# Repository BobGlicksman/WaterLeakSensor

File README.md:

# WaterLeakDetector - Version 2
The Water Leak Detector (WLD) is an IoT device that can monitor two specific locations for the presence of water. 
When water is detected, an alarm will sound and an SMS text alert will be sent to the user's mobile phone. 

A typical use case is to deploy the WLD in a laundry room where it can monitor water leaks that might occur from a washing machine, 
hot water heater, or sewer backup.

The WLD also includes a temperature and humidity sensor. These values are displayed on a dial and also in a smartphone app.  The
smartphone app (Android only at this time) is included in this project.  High and low temperature limits may be set via the smartphone
app.  When either limit is hit, an SMS text alert will be sent to the user's mobile phone.  The smartphone app allows the user to set the
high and low temperature limits.  The app displays the current temperature, relative humidity, and the status of all three alarms (low
temperature, high temperature, water leak).

This version (version 2) of the WLD eliminates Blynk and IFTTT integrations in favor or our current standard techniques for app development,
alarms and alerts, and for logging to Google cloud spreadsheets.  For details, see: 

https://github.com/TeamPracticalProjects/Connectivity_Tools_with_Particle_Devices

Begin with the file WLD Read Me First.pdf

<!---  -->

<!---  -->

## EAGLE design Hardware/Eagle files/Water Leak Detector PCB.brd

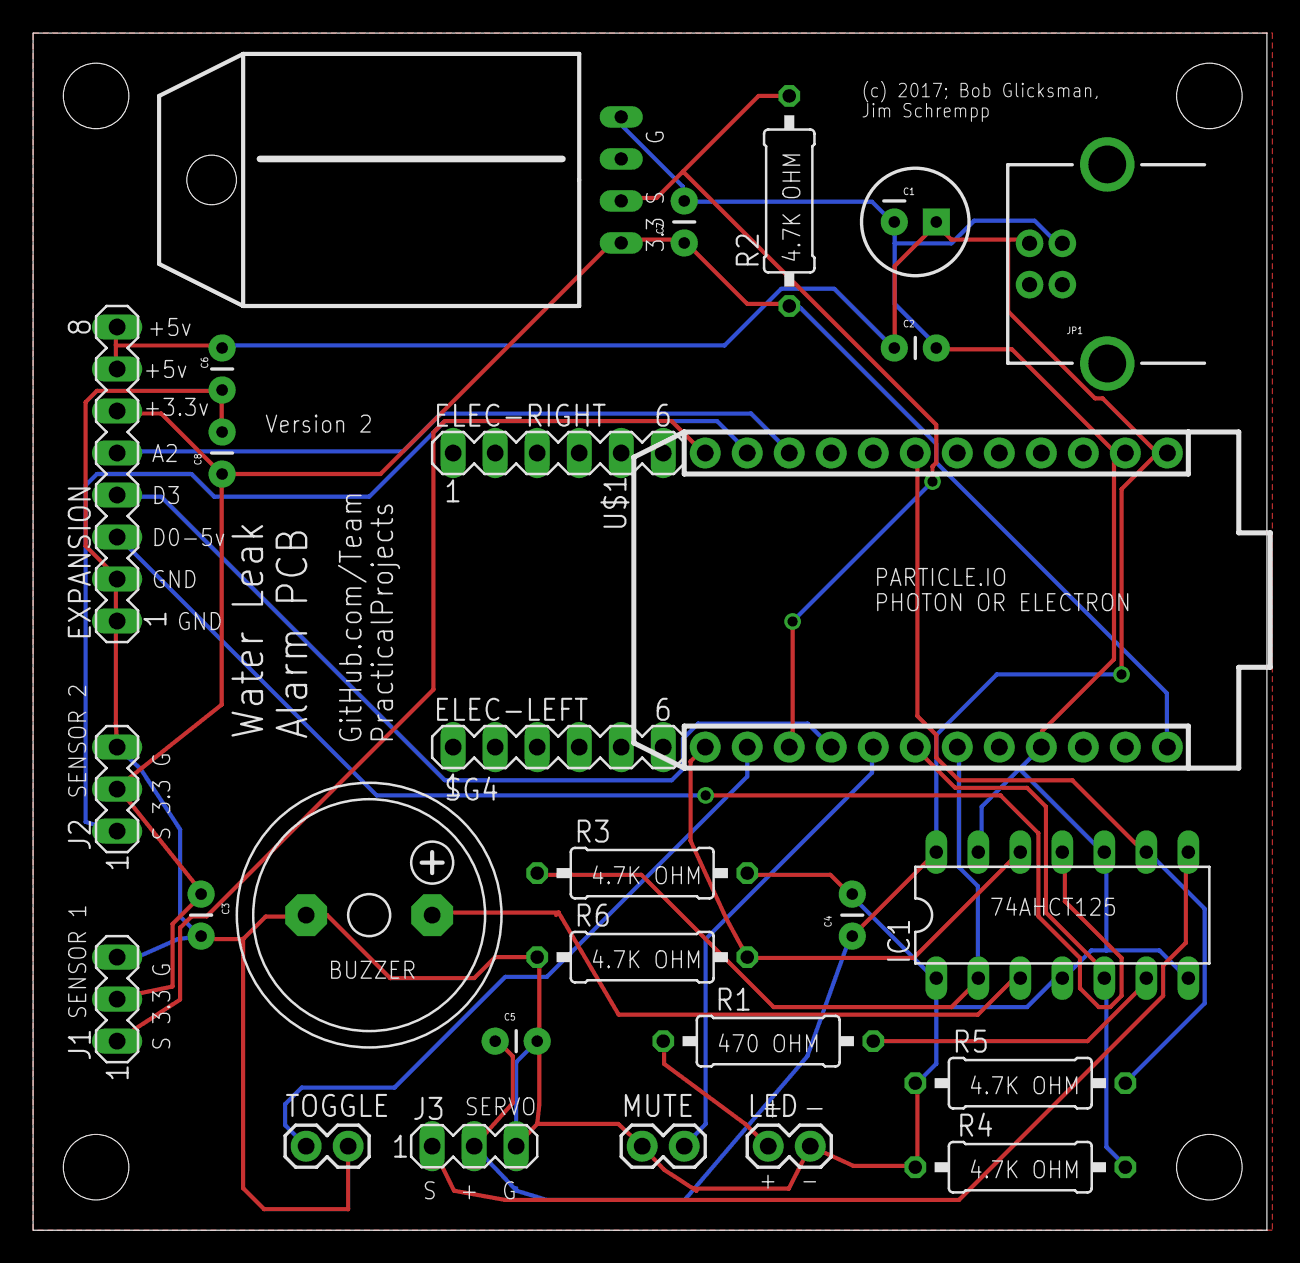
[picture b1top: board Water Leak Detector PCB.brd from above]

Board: 2 copper layers, 74.6 x 72.4 mm, 28 parts (0 on the bottom side), 19 nets.

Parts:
C1: 100uf; CPOL-RADIAL-100UF-25V
C2, C3, C4, C5, C6, C7, C8: 0.1 uF; CAP-PTH-SMALL
ELEC-LEFT: MA06-1
ELEC-RIGHT: MA06-1
EXPANSION: MA08-1
IC1: 74AHCT125; DIL14
J1: Sensor 1; MA03-1
J2: Sensor 2; MA03-1
J3: SERVO; MA03-1
JP1: USB-B; USB-B-PTH
LED: 1X02
MUTE: 1X02
R1: 470; 0309/12
R2, R3, R4, R5, R6: 4.7K; 0309/12
SG4: F/HMB
TOGGLE: 1X02
U$1: PHOTON_WITH_HEADERS; PHOTON
U$2: DHT22

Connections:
+3.3V: C3.1, C7.1, C8.1, EXPANSION.6, J1.2, J2.2, R2.1, U$1.24, U$2.VDD
GND: C1.2, C2.2, C3.2, C4.2, C5.2, C6.2, C7.2, C8.2, EXPANSION.1, EXPANSION.2, IC1.1, IC1.4, IC1.7, IC1.10, IC1.13, J1.3, J2.3, J3.3, JP1.GND, LED.2, MUTE.1, R3.2, R4.2, R5.1, R6.1, SG4.-, TOGGLE.2, U$1.2, U$1.21, U$2.GND
unnamed: IC1.8, J3.1
unnamed: J2.1, U$1.11
unnamed: J1.1, U$1.12
unnamed: IC1.2, R3.1, U$1.19
unnamed: IC1.3, SG4.+
unnamed: IC1.9, R5.2, U$1.7
unnamed: IC1.6, R1.1
unnamed: LED.1, R1.2
unnamed: MUTE.2, U$1.17
unnamed: EXPANSION.4, U$1.16
unnamed: EXPANSION.3, IC1.11
unnamed: EXPANSION.5, U$1.10
unnamed: IC1.12, R6.2, U$1.13
unnamed: R2.2, U$1.15, U$2.DATA
unnamed: TOGGLE.1, U$1.14
unnamed: IC1.5, R4.1, U$1.18
VCC: C1.1, C2.1, C4.1, C5.1, C6.1, EXPANSION.7, EXPANSION.8, IC1.14, J3.2, JP1.VBUS, U$1.1

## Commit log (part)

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2017-01-19 :lollipop: Added .gitattributes & .gitignore files
2017-01-19 In process develop-and-test
    This test code reads sensor values every 3 seconds and thresholds and
    integrates the thresholded values to test software filtering for
    reliable water level detection and alarming.
2017-01-20 Added documents
    Added preliminary (incomplete) parts list, final concept document and
    sensort test report
2017-01-21 Added pushbutton debouncing
2017-01-21 Updated parts list
    Added in new, cheaper source for water level sensor on Amazon.com
2017-01-25 Removed redundent variable definition
    Removed redundent variable definition from version 04.
2017-01-26 Added new alarm detection and publication
    Added to development version 04. Tested OK with Partcile console and
    with IFTTT.
2017-01-31 added PDF version of full schematic
    PDF is the same as the eagle .sch version
2017-01-31 Updates schematic
    Added pullup resistor required for DHT11.
2017-02-02 Added support for two sensors and cleaned up directory
    Version 05 adds support for two sensors. Deleted the older test
    firmware versions. This version 05 is the one version that tests all
    leak sensor detection and alarming functions.
2017-02-02 Added Water Leak Detector firmware
    Water leak Detector is to be the released version of the firmware for
    this project. This commit contains completed and tested, full speed
    water leak detection and alarming code. The final project still needs
    DHT11, meter, and Blynk support.
2017-02-03 Deleted test program from development branch
2017-02-03 Deleted all but test code in this branch
2017-02-03 Reorganized
    Added folders for hardware, Firmware and Documentation and moved files
    appropriately.
2017-02-03 Moves Sensor test report to this branch
2017-02-06 Added test code for DHT11
    The ADA version uses the Adafruit library and it works. The PIE version
    uses the Piettetch library and it does not work. The latter appears to
    never return from dth.acquireAndWait() and even tends to put the Photon
    into an unhappy state (breathing green) from which I have to fiddle with
    the buttons to even get it to OTA flash new code!
2017-02-07 Changed sensor pin to D2
    The Piettetech library does not seem to work with the sensor on D0. It
    works on D2 and this version changes the data pin accordingly.
2017-02-07 Updated schematic
    Changed DHT11 data to Photon D2 instead of D0. D0 does not work with
    Piettetech library. Changed IC1D input to D0 to free up D2 for the
    DHT11.
2017-02-08 Added Servo test code
2017-02-08 Updated schematic
    Placed 5.6 Kohm pulldown resistors on all input pins of the 74AHCT125 to
    clamp off noise when the Photon is flashing/reset. Used 5.6 Kohm in
    lieu of 4.7 Kohm because that is what I had on hand.
2017-03-03 junk commit
2017-03-03 remove junk files
2017-03-07 Added routine to calibrate the servo meter
    This routine uses the SIS debug client to allow the user to exercise the
    servo with different values and to find the proper endpoint values for
    any given servo when mounted with the meter scale.
2017-03-07 Added Calibration Document
    This document describes the theory behind calibrating and scaling
    temperature and humidity to read out on the servo meter. It also
    describes the calibration and scaling testing procedure that must be
    used to obtain the values of MAX_POS and MIN_POS for any given servo.
2017-03-08 Changed servo control pin to A5
    Changed the servo control pin from D3 to A5 for compatibility with Core,
    Photon and Electron (according to Particle documentation).
2017-03-09 bezel v0.3 better Celcius marks
2017-03-16 Published integrated code
    This software integrates the water leak detection and alarm code with
    the code that reads the DHT11 and publishes/displays the values.
    Publications are to the particle cloud. This may be changed to Blynk
    for the release.
2017-03-16 moved ServoCal to new folder. Changed return code so that actual servo position is returned if a limit is exceeded
2017-03-16 added two new cloud methods: pos plus 5 and pos minus 2. Makes it easier to dial in the correct limits.
2017-03-16 renamed WaterLeakDetector to .ino for easier development
2017-03-16 added editorconfig file for tabs
2017-03-16 Update .editorconfig
    tried another way to get this working
2017-03-16 includes the DHT library reference
2017-03-17 changed particle publish events to use stable event names and the value in the data field
2017-03-18 smoothed the display values with 10 point moving average
2017-03-21 Minor updates to comments
2017-03-22 Updated comments
    Updated comments to reflect smoothing; deleted old commented out
    publication code.
2017-03-24 v0.5 made 0.7l box dial large enough to fill box top.
2017-03-24 Blynk is basically working.
2017-03-27 Added integrated code from Development branch to this branch
    I added this code to this branch to preserve a copy of the integrated
    and tested firmware before Blynk integration is added to the release
    firmware in development. It is handy to not need Blynk for hardware
    development activities (PC board, packaging, cabling development). This
    firmware may be removed from this branch after the final hardware
    development is completed or perhaps sooner, when Blynk integration may
2017-03-27 put ifdef's around the blynk code so it can be easily disabled
2017-03-28 Added breadboard schematic
    Added the Eagle file and PDF version of the schematic for the breadboard
    for archival purposes.
2017-03-28 Added PCB Eagle Files - NOT COMPLETE
    Saving work-in-process PCB files
2017-04-06 Updated schematic
    Changed mini screw terminals to pin headers. Completed board placement
    and routing, but still need the ground pour.
2017-04-07 Optimized and routed PCB
    Still must perform the ground pour and create silk screen.
2017-04-07 Deleted in-process eagle PCB files
    The final files have been placed in the development branch
2017-04-07 Moved PCB files to the correct folders for publication
2017-04-08 Updated parts list
    Need to order parts and verify correct footprints for all (particularly
    the piezzo buzzer).
2017-04-08 Updated parts list
2017-04-22 Updated schematic
    Updated schematic to show the resistor values for the components that
    are on the parts list.
2017-04-28 Test version with Blynk
    This is ^im's version of WLD with Blynk integration. I changed the
    Particle.publish() time to 8 seconds for easier console debugging. I
    put my Blynk auth code in this version, so do not copy to Master without
    deleting the auth code!!! I also disabled IFTTT notify, since Blynk
    notify is working.
2017-05-01 Added second Blynk notification
    After Blynk notification of an alarm, a second notification will be sent
    30 seconds later. This is to help ensure reliability for receiving a
    WLD alarm.
2017-05-03 version 0.6
2017-05-04 added a mounting bracket
2017-05-22 mount v0.2 prior to cutting
2017-05-24 Updated parts list
    Updated the parts list to add a link for the PCB
2017-05-30 Blynk Terminal and LED added. Need Blynk app of 5/30/2017 or later
2017-06-01 untested. includes Bob's fix
2017-07-06 v0.4 of the mount. RJ11 mounts now correct. Lowered wall mount holes a bit.
2017-07-06 bezel 1.0 with toggle indexing slot
2017-08-02 case bottom version 2. PCB mounting standoffs. bezel retention corners.
2017-08-02 added backup files to gitignore
2017-08-03 added the Aug 3 version of Blynk app setup
2017-08-05 Blynk doc updated to show widget configuration
2017-08-05 smaller image and new one of app
2017-08-09 Updated Parts List
    Still missing a few links from Jim: V2 PCB, Shapeways, small mounting
    screws for 3D faceplate. This version of the parts list specifies Nylon
    4-40 hardware (metal or nylon 6-32 hardware can also be used). It also
    specifies a jameco 7 foot telephone cable with a note about other
    lenghts and colors being available in hardware stores.
2017-08-15 updated CaseDial to have smaller cut out for servo, and organized laser cut case pages. This case was actually cut and assembled.
2017-08-18 Updated Parts List
    Updated the parts list and prublished as PDF. Moved from Hardware to
    Documentation.
2017-08-20 wood case v0.6 makes it larger to give standoffs clearance from PCB
2017-09-02 Updated docs for release
    Only some docs have been updated and reviewed for release. This folder
    is not yet complete for release.
2017-09-05 Added Firmware Installation document
2017-09-06 Updated Servo Meter Calibration doc
    Reorganized to show the procedure up front and the theory at the end.
    Changes Shrimpware debug instructions to Particle console instructions.
    Formatted doc for publication.
2017-09-06 Finalized document
2017-09-06 Finalized
2017-09-07 Deleted Prepare Your Photon doc
    deleted per agreement with Jim -- already covered in FW Installation doc
2017-09-13 Cleanup and postin of Read Me First document
    Deleted the Photo folder. Updated the .MD file. Posted draft of WLD
    Read Me First to the top level of this repository and deleted older Read
    me First doc from the Documentation folder.
2017-09-13 Restored Photos folder for ReadMed.MD pics
2017-09-13 v3 with cylndrical standoffs (again).
2017-09-13 Finalized Read Me First and deleted redundant doc
    Updated per Jim's review. Deleted old Troubleshooting doc
2017-09-14 Finalized documentation
    Updated and checked all links. Checked spelling and updated TOC.
2017-09-14 Updated comments to reflect use of console
    Uodated the comments and tested the firmware again by compiling and
    flashing to my WLD
2017-09-20 Create README.MD
    A note about PDFs not displaying correctly in GitHub on some browsers.
2021-03-20 Update WaterLeakDetector.ino
    Commented out Particle.publish() for temp and humidity because of Particle's new pricing policy. Updated PietteTech_DHT and Blynk libraries to the latest version and compiles and flashes OK. However,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
2022-10-22 Create Alarm Class templates
    No code yet - WIP
2022-10-23 Created project
    Created a valid particle project and copied the latest code into it.
2022-10-23 Added PietteTech_DHT library
2022-10-23 Completed coding Alarm Processor
2022-10-24 Update WLDAlarmProcessor.cpp
    Cleaned up code. Publish full text strings for alarms.
2022-10-24 Update WLDAlarmProcessor.cpp
    fixed bugs
2022-10-25 Tested Alarm Class Files
2022-10-25 Update WaterLeakDetector.ino
    Incomplete
2022-10-25 Update WLDAlarmProcessor.h
    Changed to real one day definition from testing mode
2022-10-26 version 2.0 tested
    This new code is tested and working EXCEPT for EEPROM. Data from EEPROM always reads back as zero.
2022-10-26 Version 2.0 working except EEPROM
    still trying to get EEPROM working - no joy.
2022-10-27 Version 2.0 WIP
    Still no joy on EEPROM
2022-10-27 WLD version 2.0
    Looks like all bugs are corrected
2022-10-28 WLD version 2.01
    Completed and tested. Temp alarm limits now stored in EEPROM and restored upon reboot. Eliminated the initial low temp alarm on reboot, Formatted the temp and humidity cloud variables to read out to 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
2022-11-09 Create Alarm_Script.txt
    Initial release v1.0 of alarm script (Google Apps Script)
2022-11-16 updated git ignore, deleting a bunch of files
2022-11-16 update gitignore
2022-11-27 App is complete
    Source (.aia) and install package (.apk) are included
2022-12-03 Changed Photo of Blynk to new App
2022-12-04 V2 Concept Document
    Revised the concept document for version 2.
2022-12-22 Deleted obsolete manuals
2022-12-23 Update WLD Troubleshooting.pdf
    Minor edits to bring the document up to date with V2
2022-12-24 Update WLD Troubleshooting.pdf
    Updated per Jim's comments.
2022-12-25 Update WLD Read Me First.pdf
    Updated for V2

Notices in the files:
Hardware/Eagle files/Water Leak Detector PCB.brd:
(c) 2017; Bob Glicksman,
Jim Schrempp
parts and their libraries:
SparkFun-Capacitors: Licensing: CC v3.0 Share-Alike You are welcome to use this library for commercial purposes.
SparkFun-Passives: Licensing: Creative Commons ShareAlike 4.0 International - https://creativecommons.org/licenses/by-sa/4.0
